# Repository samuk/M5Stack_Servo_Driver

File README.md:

# M5Stack_Servo_Driver

PCA9685 Servo Driver Shield for M5Stack

## Schematics

## Servo Driver: PCA9685 (NXP Semiconductors)
[Datasheet](https://www.nxp.com/docs/en/data-sheet/PCA9685.pdf)

## Arduino IDE Library (Adafruit-PWM-Servo-Driver)
[Adafruit-PWM-Servo-Driver](https://github.com/adafruit/Adafruit-PWM-Servo-Driver-Library)

**Change I2C address to 0x72**

## Example
M5Stack_Plotclock

https://github.com/tomorrow56/M5Stack_Plotclock

## Support
https://thousandiy.wordpress.com/2018/10/20/servo-driver-shield-for-m5stack/

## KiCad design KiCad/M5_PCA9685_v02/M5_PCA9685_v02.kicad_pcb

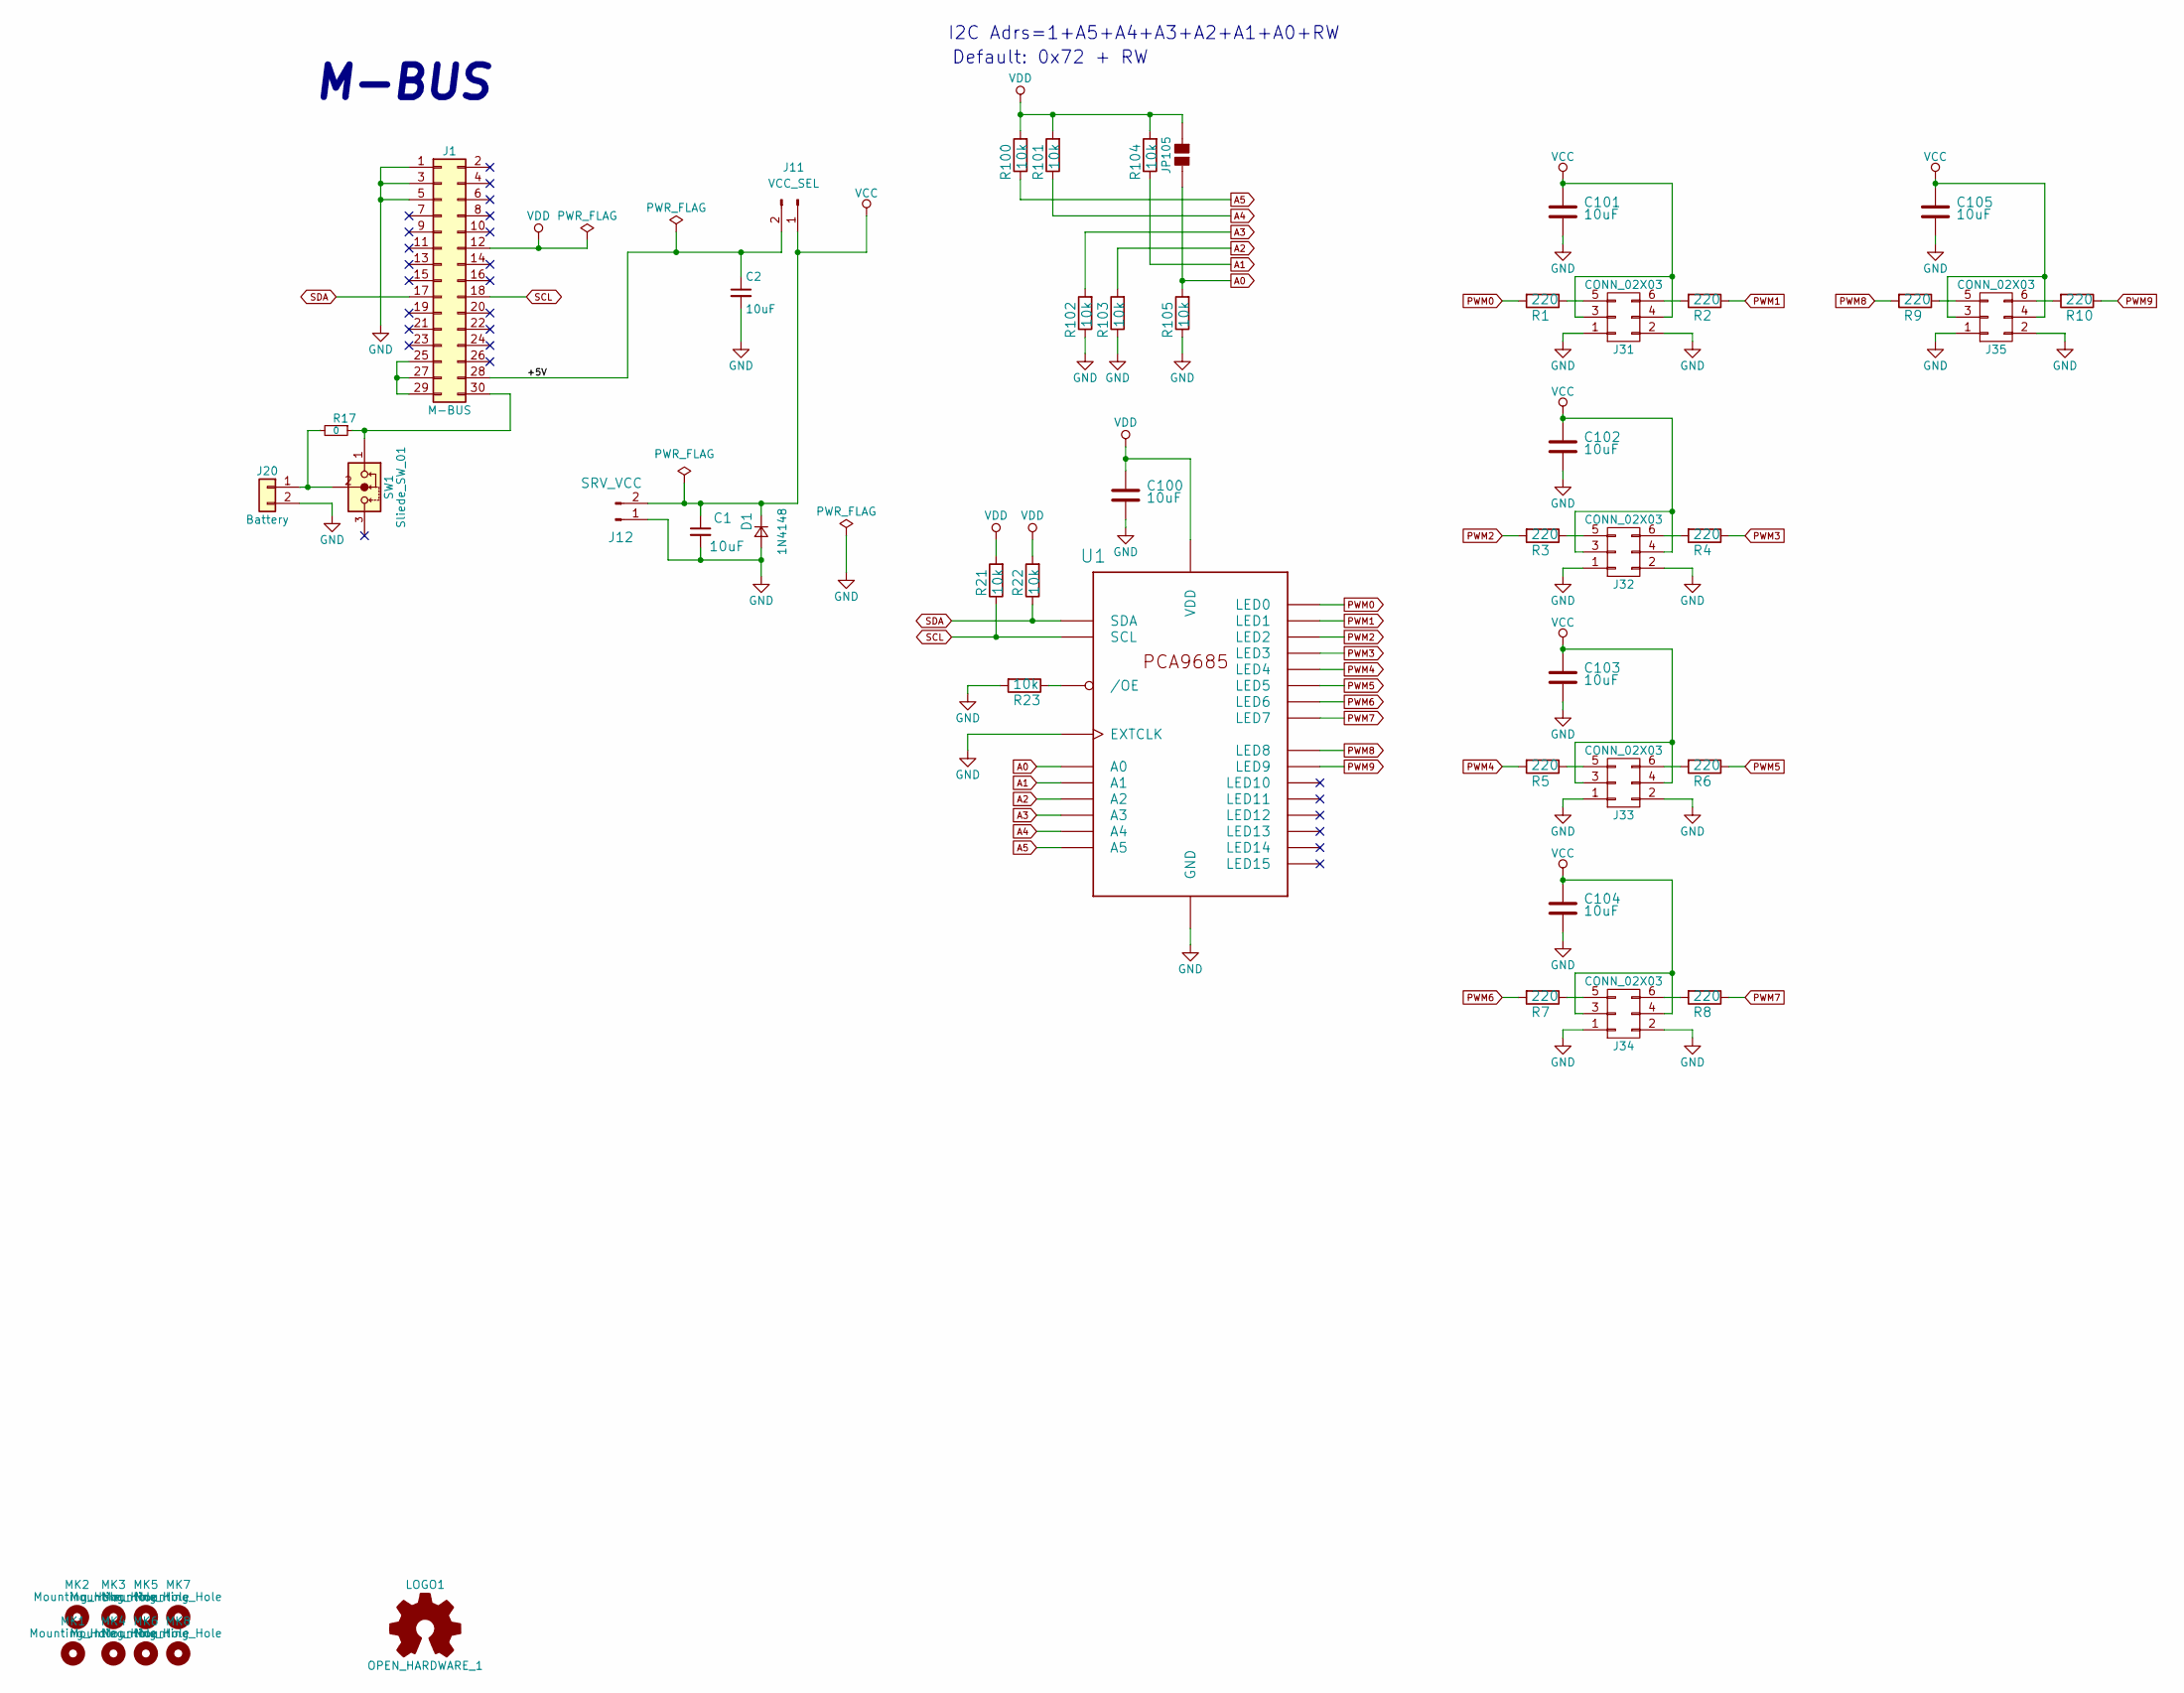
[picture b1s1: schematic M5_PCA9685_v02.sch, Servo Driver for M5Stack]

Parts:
C1, C2, C100, C101, C102, C103, C104, C105: 10uF; C_0603
D1: 1N4148; D_SOD-323
J1: M-BUS; Pin_Header_MBUS_SMD_TH
J11: VCC_SEL; Pin_Header_Angled_1x02_Pitch2.54mm
J12: SRV_VCC; Pin_Header_Angled_1x02_Pitch2.54mm
J20: Battery; Pin_Header_Angled_1x02_Pitch2.54mm
J31, J32, J33, J34, J35: CONN_02X03; Pin_Header_Angled_2x03_Pitch2.54mm
JP105: SOLDERJUMPER; SOLDERJUMPER_REFLOW
LOGO1: OPEN_HARDWARE_1; OSHW-logo_silkscreen-front_3mm
MK1, MK2, MK3, MK4: Mounting_Hole; MountingHole_3.2mm_M3
MK5, MK6, MK7, MK8: Mounting_Hole; MountingHole_2.2mm_M2
R1, R2, R3, R4, R5, R6, R7, R8, R9, R10: 220; R_0603
R17: 0; R_0603
R21, R22, R23, R100, R101, R102, R103, R104, R105: 10k; R_0603
SW1: Sliede_SW_01; slide_switch_angled
U1: PCA9685; PCA9685_TSSOP28

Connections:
/+5V: C2.1, J1.28, J11.2
A0: JP105.2, R105.2, U1.1 (A0)
A1: R104.1, U1.2 (A1)
A2: R103.2, U1.3 (A2)
A3: R102.2, U1.4 (A3)
A4: R101.1, U1.5 (A4)
A5: R100.1, U1.24 (A5)
GND: C1.2, C2.2, C100.2, C101.2, C102.2, C103.2, C104.2, C105.2, D1.2 (A), J1.1, J1.3, J1.5, J12.1, J20.2, J31.1, J31.2, J32.1, J32.2, J33.1, J33.2, J34.1, J34.2, J35.1, J35.2, R23.2, R102.1, R103.1, R105.1, U1.14 (GND), U1.25 (EXTCLK)
unnamed: J1.25, J1.27, J1.29
unnamed: J1.30, R17.1, SW1.1
unnamed: J20.1, R17.2, SW1.2
unnamed: J31.5, R1.1
unnamed: J31.6, R2.2
unnamed: J32.5, R3.1
unnamed: J32.6, R4.2
unnamed: J33.5, R5.1
unnamed: J33.6, R6.2
unnamed: J34.5, R7.1
unnamed: J34.6, R8.2
unnamed: J35.5, R9.1
unnamed: J35.6, R10.2
unnamed: R23.1, U1.23 (/OE)
PWM0: R1.2, U1.6 (LED0)
PWM1: R2.1, U1.7 (LED1)
PWM2: R3.2, U1.8 (LED2)
PWM3: R4.1, U1.9 (LED3)
PWM4: R5.2, U1.10 (LED4)
PWM5: R6.1, U1.11 (LED5)
PWM6: R7.2, U1.12 (LED6)
PWM7: R8.1, U1.13 (LED7)
PWM8: R9.2, U1.15 (LED8)
PWM9: R10.1, U1.16 (LED9)
SCL: J1.18, R21.1, U1.26 (SCL)
SDA: J1.17, R22.1, U1.27 (SDA)
VCC: C1.1, C101.1, C102.1, C103.1, C104.1, C105.1, D1.1 (K), J11.1, J12.2, J31.3, J31.4, J32.3, J32.4, J33.3, J33.4, J34.3, J34.4, J35.3, J35.4
VDD: C100.1, J1.12, JP105.1, R21.2, R22.2, R100.2, R101.2, R104.2, U1.28 (VDD)

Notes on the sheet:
I2C Adrs=1+A5+A4+A3+A2+A1+A0+RW
M-BUS
Default: 0x72 + RW

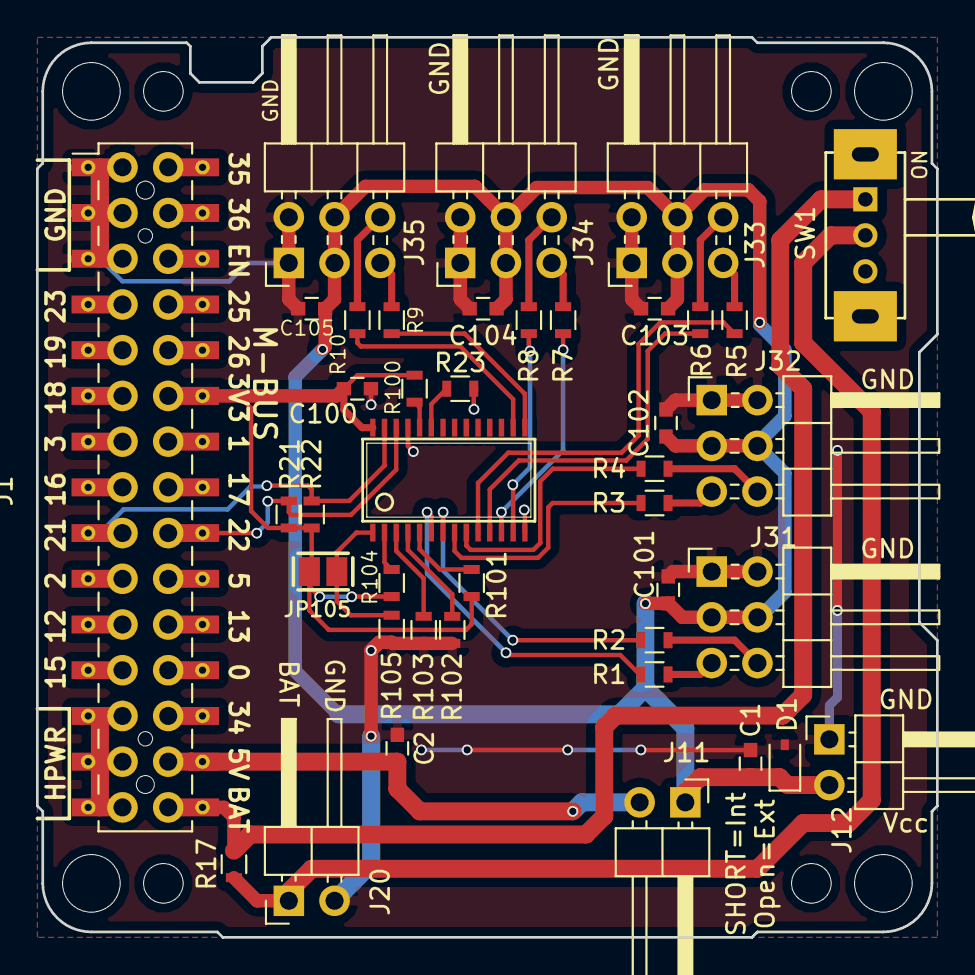
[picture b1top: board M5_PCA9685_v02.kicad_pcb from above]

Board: 2 copper layers, 50.0 x 50.0 mm, 50 parts (1 on the bottom side), 36 nets.

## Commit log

2019-04-29 add step and f3d format of case data
